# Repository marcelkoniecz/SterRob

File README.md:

# SterRob
Projekt loggera danych, logger zapisuje oraz wysyła wartości zmierzone na matrycy fotorezystorów
Autorzy: kuchnast, marcelkoniecz

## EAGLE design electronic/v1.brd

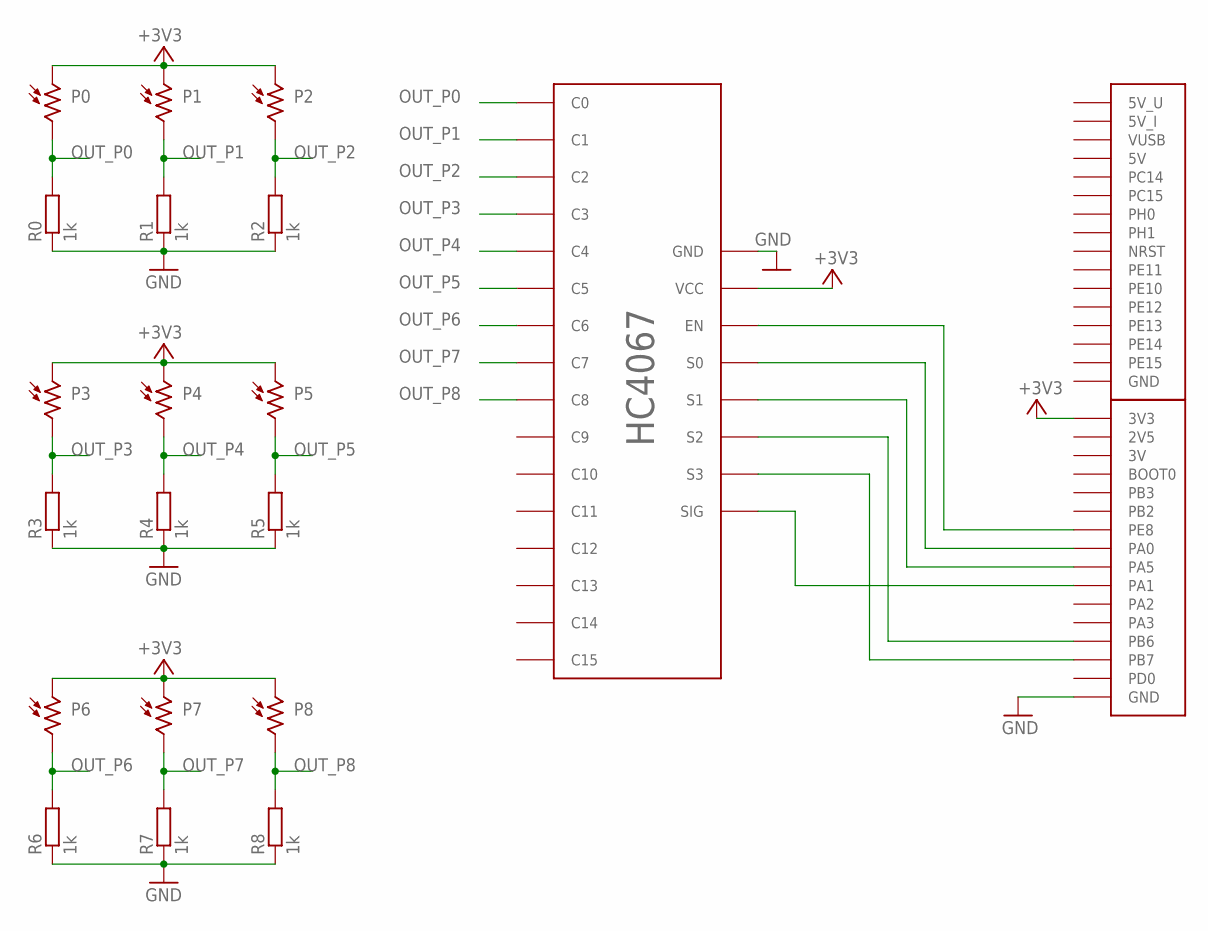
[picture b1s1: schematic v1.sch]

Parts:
P0, P1, P2, P3, P4, P5, P6, P7, P8: PHOTORESISTOR
R0, R1, R2, R3, R4, R5, R6, R7, R8: 1k; 0207/10
U$1: STM32L476_DISCOVERY
U$2: HC4067_BREAKOUT_BOARD; ANALOG_MUX_BREAKOUT_HC4067

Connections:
2V5: U$1.2V5
3V: U$1.3V
5V_I: U$1.5V_I
5V_U: U$1.5V_U
+3V3: P0.P1 (1), P1.P1 (1), P2.P1 (1), P3.P1 (1), P4.P1 (1), P5.P1 (1), P6.P1 (1), P7.P1 (1), P8.P1 (1), U$1.3V3
GND: R0.1, R1.1, R2.1, R3.1, R4.1, R5.1, R6.1, R7.1, R8.1, U$1.GND_1 (GND), U$1.GND_2 (GND), U$1.GND_3 (GND), U$1.GND_4 (GND), U$2.GND
unnamed: U$1.PE8, U$2.EN
unnamed: U$1.PA0, U$2.S0
unnamed: U$1.PA5, U$2.S1
unnamed: U$1.PB6, U$2.S2
unnamed: U$1.PB7, U$2.S3
unnamed: U$1.PA1, U$2.SIG
OUT_P0: P0.P2 (2), R0.2, U$2.C0
OUT_P1: P1.P2 (2), R1.2, U$2.C1
OUT_P2: P2.P2 (2), R2.2, U$2.C2
OUT_P3: P3.P2 (2), R3.2, U$2.C3
OUT_P4: P4.P2 (2), R4.2, U$2.C4
OUT_P5: P5.P2 (2), R5.2, U$2.C5
OUT_P6: P6.P2 (2), R6.2, U$2.C6
OUT_P7: P7.P2 (2), R7.2, U$2.C7
OUT_P8: P8.P2 (2), R8.2, U$2.C8
VCC: U$2.VCC
VUSB: U$1.VUSB

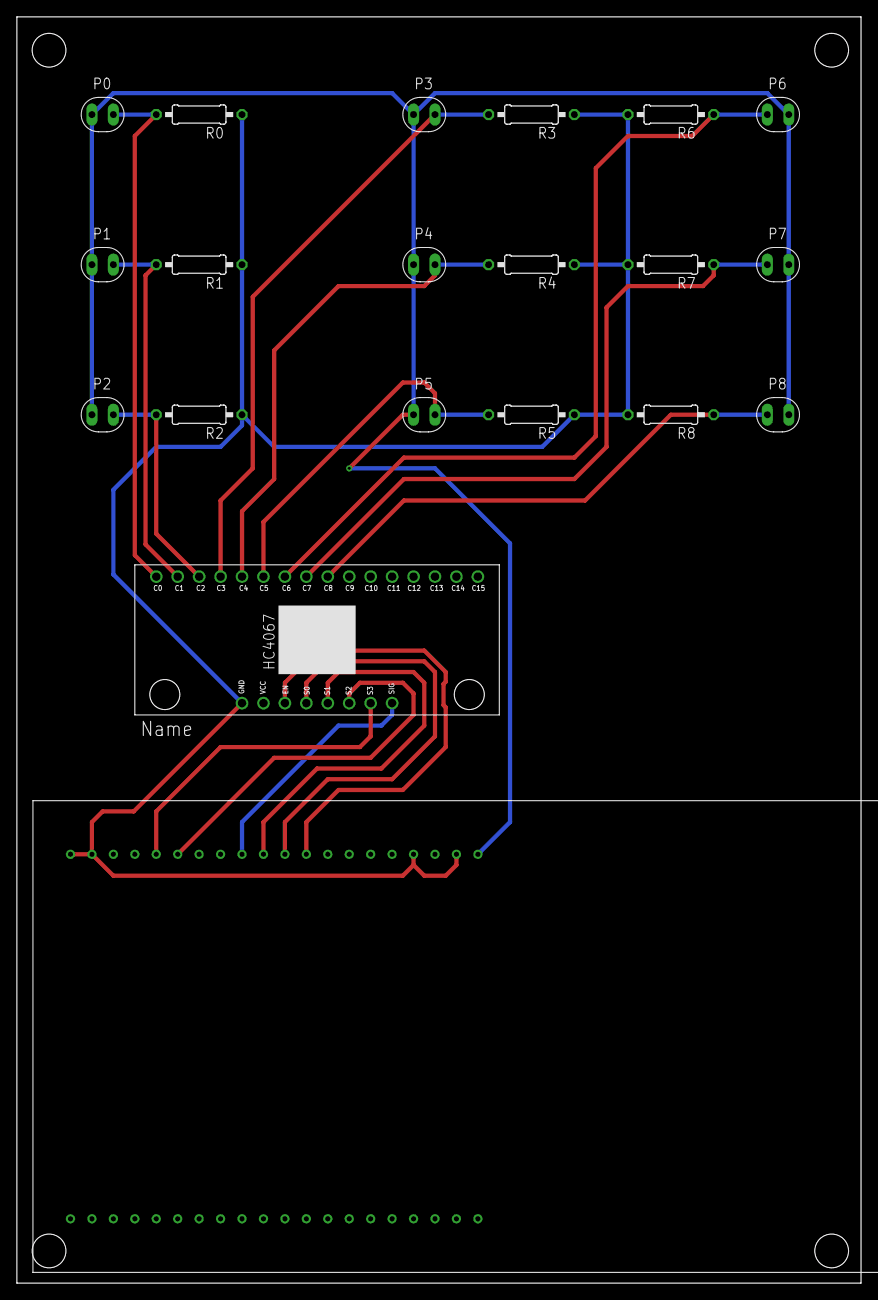
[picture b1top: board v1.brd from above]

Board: 2 copper layers, 100.0 x 150.0 mm, 20 parts (0 on the bottom side), 17 nets.

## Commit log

2022-04-04 Test
2022-04-04 Added RTC functions
2022-04-14 Added QSPI Bib
2022-04-15 added new source file - operations.c
2022-04-16 added sendData function
2022-04-17 Tested qspi
2022-04-19 Time function exaple
2022-04-22 Tests
2022-04-24 Add electronic diagrams and measurement tests
2022-04-25 Add UART DMA communication and basic
2022-04-25 Cleaned
2022-04-25 Add parser and some functions to manipulate readings
2022-05-13 Simple flask server test
2022-05-13 Flask commit
2022-05-13 First website
2022-05-15 Changes in STM Reciver
2022-05-15 Some python scripts and rework of stm uart parser
2022-05-15 Reciver commands ready
2022-05-16 Revert "Reciver commands ready"
    This reverts commit dce43a9587676671462cfe6570bb2ed90160eb2d.
2022-05-16 Simple website
2022-05-16 Page template
2022-05-16 Working time set and get commands
2022-05-16 Testing measurements reciving
2022-05-25 Some changes
2022-05-27 made website
2022-05-28 Add measurements operations
2022-05-28 ready website
2022-05-28 Working basic functions on page
2022-05-29 Working page
2022-05-30 Last updates on website
2022-05-30 Proba
2022-05-30 Working project
2022-06-10 Final version with no restart when UART connect/disconnect
